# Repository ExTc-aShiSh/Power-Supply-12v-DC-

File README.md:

# 🔌 230V AC to 12V DC Rectifier PCB (KiCad)

This repository contains my **first-ever PCB design**(done way back in second semester), created using **KiCad** 🎉  
The project is a **230V AC to 12V DC rectifier circuit** with a built-in filtering stage, designed to convert mains AC into a smooth DC output suitable for low-voltage electronics.

> ⚠️ **Warning:** This project involves **230V AC mains voltage**. Handle with extreme care. Do not build or test this circuit unless you are familiar with proper high-voltage safety practices.

---

## 🔧 Circuit Overview

The circuit performs the following functions:
1. Steps down mains voltage  
2. Converts AC to DC  
3. Filters the DC output for smoother operation

### 🔹 Circuit Highlights

| Component | Quantity / Specification | Function / Description |
| :--- | :--- | :--- |
| **Step-down Transformer** | 230V AC → 12V AC | Converts mains AC to 12V AC |
| **Diodes** | 4× 1N4001 | Configured as a full-bridge rectifier |
| **Capacitors** | 2× Filtering Capacitors | Smooths and filters rectified DC |
| **Resistor** | 1× Current Limiter | Limits current for indicator LED |
| **LED** | 1× Output Indicator 💡 | Indicates DC output status |

---

## 📁 Repository Contents

- KiCad **schematic** files  
- KiCad **PCB layout** files  
- Supporting project files for PCB fabrication

---

## 🖥️ View the Schematic & PCB Online

You can view the **schematic** and **PCB design** directly in your browser without installing KiCad:

👉 https://kicanvas.org

Upload or link this repository to KiCanvas to explore the design interactively.

---

## 🎯 Project Goals

- Learn PCB design basics  
- Understand AC–DC rectification  
- Gain hands-on experience with KiCad  
- Build confidence in hardware design

---

## 🚀 Possible Future Improvements

- Add voltage regulation (linear or SMPS)
- Include fuse, MOV, and protection circuitry
- Improve filtering and ripple reduction
- Enhance silkscreen labels and layout

---

## 📜 License

This project is licensed under the **MIT License**.  
You are free to use, modify, and distribute this project with proper attribution.

See the `LICENSE` file for more details.

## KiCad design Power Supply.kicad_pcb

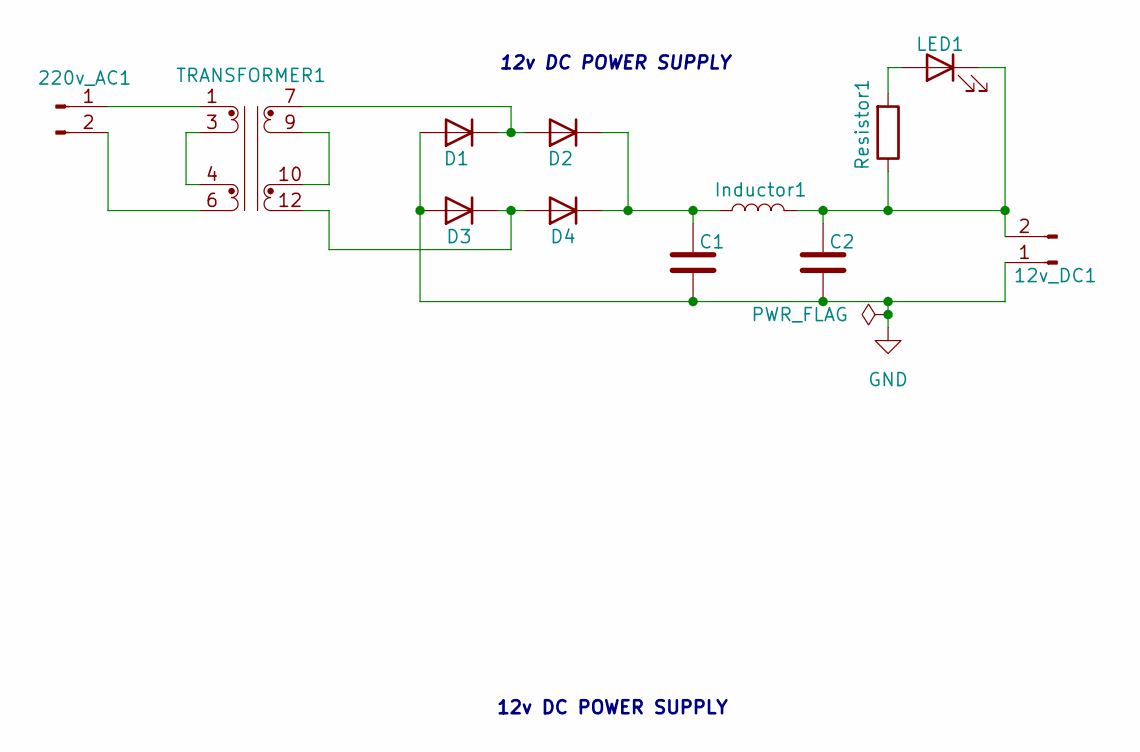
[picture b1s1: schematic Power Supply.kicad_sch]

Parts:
12v_DC1: PhoenixContact_MSTBA_2,5_2-G-5,08_1x02_P5.08mm_Horizontal
220v_AC1: TerminalBlock_Phoenix_MKDS-1,5-2-5.08_1x02_P5.08mm_Horizont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
C1, C2: C_Radial_D5.0mm_H11.0mm_P2.00mm
D1, D2, D3, D4: D_DO-41_SOD81_P10.16mm_Horizontal
Inductor1: L_Wurth_WE-HCFT-2012_LeadDiameter1.2mm
LED1: LED_D3.0mm
Resistor1: R_Axial_DIN0204_L3.6mm_D1.6mm_P7.62mm_Horizontal
TRANSFORMER1: Transformer_Triad_VPP16-310

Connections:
GND: 12v_DC1.1, C1.2, C2.2, D1.2 (A), D3.2 (A)
unnamed: 12v_DC1.2, C2.1, Inductor1.2, LED1.1 (K), Resistor1.1
unnamed: 220v_AC1.1, TRANSFORMER1.1
unnamed: 220v_AC1.2, TRANSFORMER1.6
unnamed: D1.1 (K), D2.2 (A), TRANSFORMER1.7
unnamed: C1.1, D2.1 (K), D4.1 (K), Inductor1.1
unnamed: D3.1 (K), D4.2 (A), TRANSFORMER1.12
unnamed: LED1.2 (A), Resistor1.2
unnamed: TRANSFORMER1.3, TRANSFORMER1.4
unnamed: TRANSFORMER1.9, TRANSFORMER1.10

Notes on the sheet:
12v DC POWER SUPPLY
12v DC POWER SUPPLY

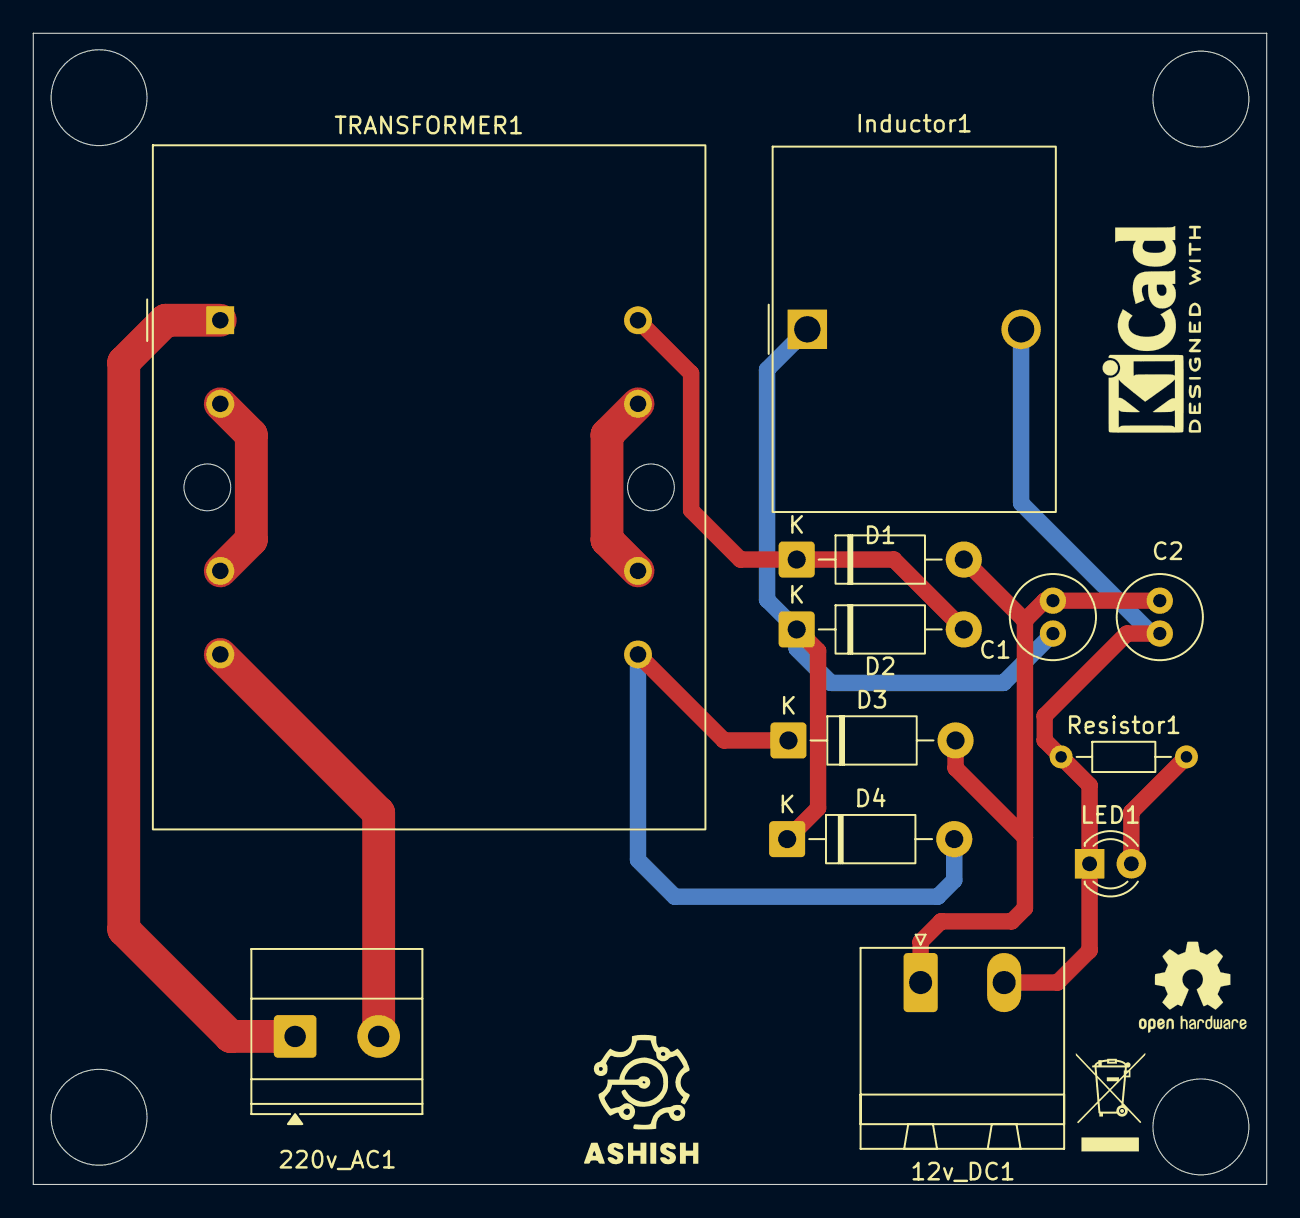
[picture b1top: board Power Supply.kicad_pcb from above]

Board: 2 copper layers, 75.0 x 70.0 mm, 12 parts (0 on the bottom side), 10 nets.

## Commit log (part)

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2026-01-02 Added design files
2026-01-02 Revise README with project details and warnings
    Updated README to provide detailed project information and safety warnings.
2026-01-02 added time reference in readme.md
    ---i did it wat before posting here---heh---
2026-03-25 edited gitignore
2026-03-25 re-routing
